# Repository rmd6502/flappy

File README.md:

flappy
======

This is the source folder for the Flappy Bird in a Box project.

Contents
--------

**circuit** Eagle files

**flappy_final_v8** Not really the final version, but the final version before github

**Arduino** Modifications for the stock Arduino 1.0.5 to enable compiling for the Flappy board.

Installation Instructions
-------------------------

* Install the [Arduino](http://arduino.cc) 1.0.5 IDE.
* Copy the libraries and hardware directories into the sketchbook directory for your platform
  * C:\Documents and Settings\My Documents\Arduino
  * ${HOME}/sketchbook
  * ${HOME}/Documents/Arduino
* Install the latest avr-gcc toolchain
  * AVR Studio from [Atmel](http://www.atmel.com) if you're on Windows,
  * sudo apt-get install avr-gcc
  * [Crosspack AVR for Mac](http://www.obdev.at/products/crosspack/index.html)
* Go to the Arduino install directory
  * C:\Program Files(x86)\Arduino
  * Not sure for linux - /usr/local/Arduino?
  * /Applications/Arduino.app
* Find the hardware/tools subdirectory
* mv the avr directory to e.g. avr.save - this is an old version of the toolchain that seems to 
have problems
* Copy or link the root of your newest toolchain as 'avr' in the hardware/tools directory.
* Restart the Arduino IDE
* You should be able to choose Flappy Board as your board type, and Dragon ISP as the programmer
* Choose "upload using programmer" instead of Upload

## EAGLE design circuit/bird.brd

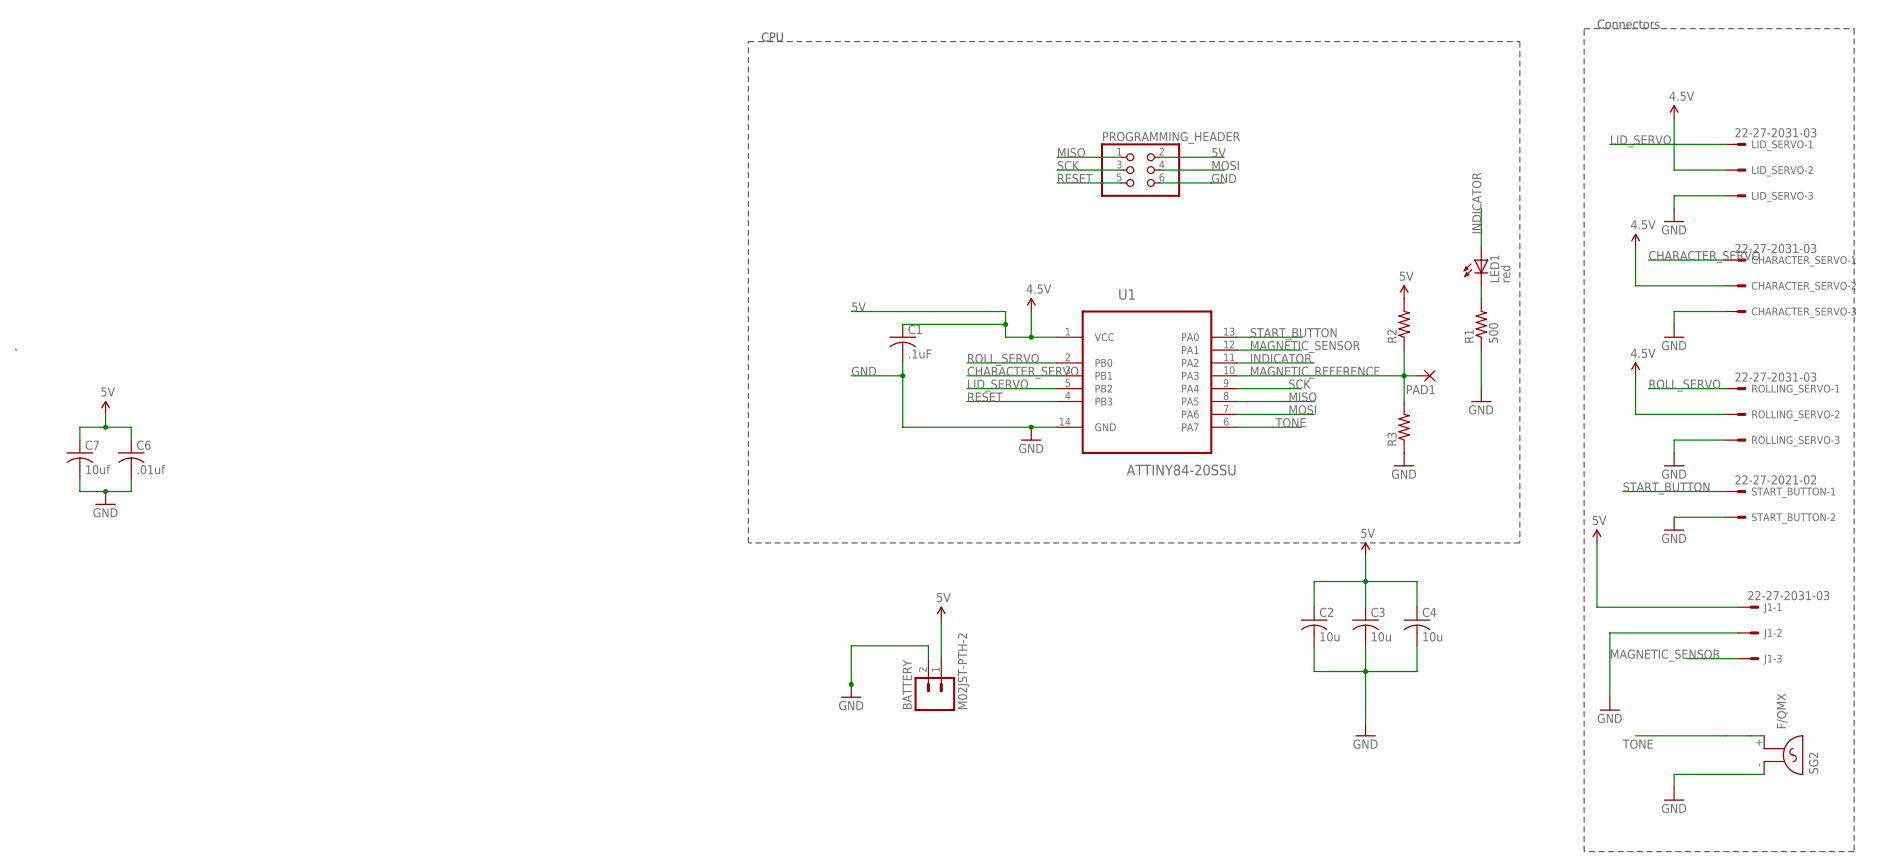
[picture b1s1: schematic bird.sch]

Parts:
BATTERY: M02JST-PTH-2; JST-2-PTH
C1: .1uF; C0603
C2, C3, C4: 10u; C0805
C6: .01uf; C0603
C7: 10uf; C0805
CHARACTER_SERVO: 22-27-2031-03; 6410-03
J1: 22-27-2031-03; 6410-03
LED1: red; SML1206
LID_SERVO: 22-27-2031-03; 6410-03
PAD1: 2,54/0,8
PROGRAMMING_HEADER: PINHD-2X3; 2X03
R1: 500; R0603
R2, R3: R-US_R0603; R0603
ROLLING_SERVO: 22-27-2031-03; 6410-03
SG2: F/QMX
START_BUTTON: 22-27-2021-02; 6410-02
U1: ATTINY84-20SSU; SOIC127P600X175-14N

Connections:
5V: BATTERY.1, C1.1, C2.1, C3.1, C4.1, C6.1, C7.1, CHARACTER_SERVO.2, J1.1, LID_SERVO.2, PROGRAMMING_HEADER.2, R2.2, ROLLING_SERVO.2, U1.1 (VCC)
CHARACTER_SERVO: CHARACTER_SERVO.1, U1.3 (PB1)
GND: BATTERY.2, C1.2, C2.2, C3.2, C4.2, C6.2, C7.2, CHARACTER_SERVO.3, J1.2, LID_SERVO.3, PROGRAMMING_HEADER.6, R1.1, R3.1, ROLLING_SERVO.3, SG2.- (1), START_BUTTON.2, U1.14 (GND)
INDICATOR: LED1.A, U1.11 (PA2)
LID_SERVO: LID_SERVO.1, U1.5 (PB2)
MAGNETIC_REFERENCE: PAD1.1, R2.1, R3.2, U1.10 (PA3)
MAGNETIC_SENSOR: J1.3, U1.12 (PA1)
MISO: PROGRAMMING_HEADER.1, U1.8 (PA5)
MOSI: PROGRAMMING_HEADER.4, U1.7 (PA6)
unnamed: LED1.C, R1.2
RESET: PROGRAMMING_HEADER.5, U1.4 (PB3)
ROLL_SERVO: ROLLING_SERVO.1, U1.2 (PB0)
SCK: PROGRAMMING_HEADER.3, U1.9 (PA4)
START_BUTTON: START_BUTTON.1, U1.13 (PA0)
TONE: SG2.+ (2), U1.6 (PA7)

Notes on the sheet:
CPU
Connectors

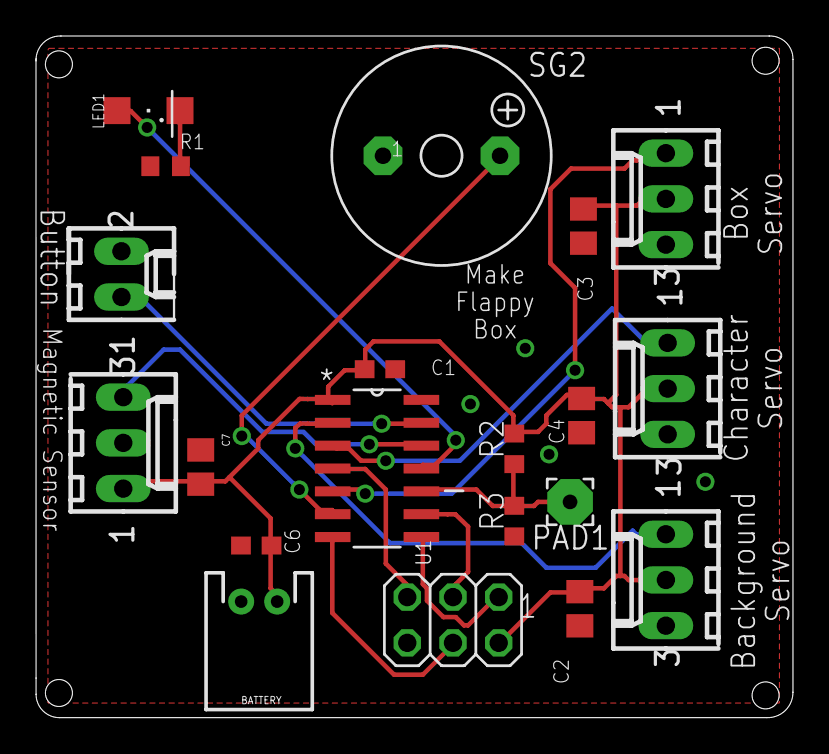
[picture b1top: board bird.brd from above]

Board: 2 copper layers, 42.1 x 37.9 mm, 20 parts (0 on the bottom side), 15 nets.

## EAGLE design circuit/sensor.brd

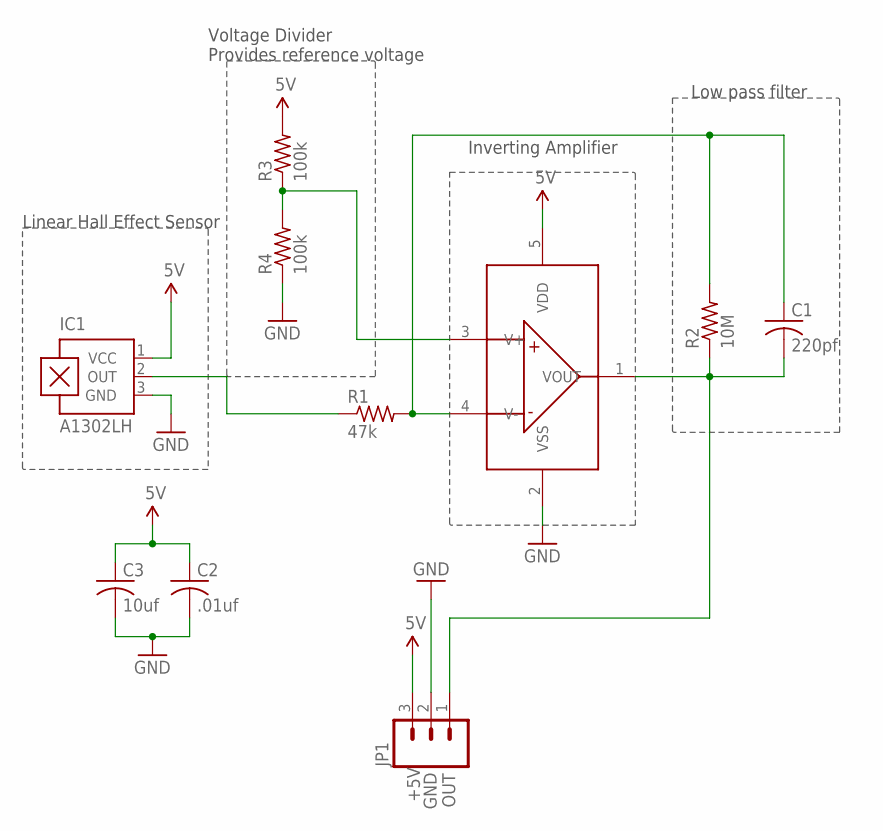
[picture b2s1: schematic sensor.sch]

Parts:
C1: 220pf; C0805
C2: .01uf; C0805
C3: 10uf; C0805
IC1: A1302LH; SOT23-W
JP1: M03PTH; 1X03
R1: 47k; R0805
R2: 10M; R0805
R3, R4: 100k; R0805
U$1: MCP601; SOT23-5

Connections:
5V: C2.1, C3.1, IC1.1 (VCC), JP1.3, R3.2, U$1.5 (VDD)
GND: C2.2, C3.2, IC1.3 (GND), JP1.2, R4.1, U$1.2 (VSS)
unnamed: C1.2, JP1.1, R2.1, U$1.1 (VOUT)
unnamed: IC1.2 (OUT), R1.1
unnamed: C1.1, R1.2, R2.2, U$1.4 (V-)
unnamed: R3.1, R4.2, U$1.3 (V+)

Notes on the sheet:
+5V
GND
OUT
Linear Hall Effect Sensor
Voltage Divider Provides reference voltage
Low pass filter
Inverting Amplifier

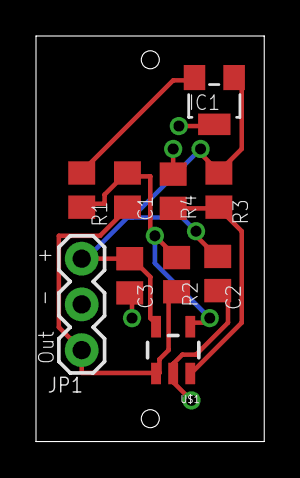
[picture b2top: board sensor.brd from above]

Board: 2 copper layers, 12.7 x 22.5 mm, 10 parts (0 on the bottom side), 6 nets.

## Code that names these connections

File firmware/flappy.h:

const int start_button = 0;
const int hall_input = 1;
const int led = 2;
const int adc_reference = 3;
const int sck = 4;
const int miso = 5;
const int mosi = 6;
const int speaker = 7;
const int lid_servo = 8;
const int character_servo = 9;
const int roll_servo = 10;

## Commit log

2014-02-23 add circuit
2014-02-23 add eagle project file
2014-02-23 update circuit to add programming header
2014-02-24 a few changes
2014-02-24 add copyright
2014-02-24 add mounting holes, labels
2014-02-28 add ported sketch
2014-03-05 add LED
2014-03-24 add tinyservo library
2014-03-27 update circuit
2014-03-28 neaten board
2014-03-28 more board tweaks
2014-03-28 fix trace
2014-03-30 add test prog
2014-04-01 add servo
2014-04-20 checkout
2014-04-21 add sensor
2014-04-21 onebutton
2014-04-21 add comments
2014-04-21 add frame
2014-04-22 update sensor
2014-04-25 use constants
2014-04-26 new layout
2014-04-29 sensor update
2014-04-29 move labels
2014-05-04 cleanups and fix sketch
2014-05-04 more cleanups
2014-05-04 ground
2014-05-11 update circuit, logo
2014-05-11 logo
2014-05-12 0603 and gnd
2014-05-13 update project:
2014-05-13 bottom logo and labels
2014-05-13 add arduino mods
2014-05-18 update board
2014-06-22 tweak board
2014-08-15 mods for new board
2014-08-18 add configuration for tiny841
2014-08-19 add schematic
2014-08-19 update serial
2014-08-21 add header
2014-08-30 add tone.cpp
2014-09-01 remove opamp circuit
2014-09-01 update tiny84hall
2014-09-01 make analogRead work on 841
2014-09-02 add pads for resistors
2014-10-05 update board, use flappy defines
2014-10-08 add reed test
2014-10-16 fixes for final flappy
2014-10-23 detach all servos game end
2014-10-30 fix buzzing, full-rotation servo
2014-11-24 add 3d printed parts
2014-11-28 add opto
2014-11-28 update opto
2014-11-28 update leads
2014-11-28 update opto, add test sketch
2014-11-29 make the block a bit bigger
2014-11-30 add rack and pinion gear
2014-11-30 update distance measurements
2014-11-30 final bird position
2014-12-13 stability rack, game start
2014-12-13 lower bracket a bit
2015-01-04 add 3d files
2015-03-17 updates for arduino, new pinouts

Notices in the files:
circuit/bird.brd:
Copyright (c) 2014 Robert M Diamond, for Fawn Qiu
parts and their libraries:
SparkFun-Connectors: Licensing: Creative Commons ShareAlike 4.0 International - https://creativecommons.org/licenses/by-sa/4.0
SparkFun: Licensing: CC v3.0 Share-Alike You are welcome to use this library for commercial purposes.
